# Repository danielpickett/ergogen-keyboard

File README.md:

# Pickett46 wireless split keyboard

A 46-key MX hot-swap keyboard with one nice!nano v2 per half and ZMK firmware.
The original Ergogen switch centers, rotations and 1.5u thumb positions are
preserved. Left and right have separate, fully routed two-layer PCBs.

## Fabrication files

- [Left JLCPCB ZIP](fabrication/pickett46-left-jlcpcb.zip)
- [Right JLCPCB ZIP](fabrication/pickett46-right-jlcpcb.zip)
- [Ordering details](docs/FABRICATION.md)
- [BOM](docs/BOM.csv) and [assembly instructions](docs/ASSEMBLY.md)
- [ZMK configuration, flashing and pin mapping](docs/FIRMWARE.md)

Both boards pass KiCad **9.0.2** DRC with **zero violations and zero unconnected
items**, with no DRC exclusions. The ZIPs also pass independent Gerber parsing,
layer/drill-count checks and source/hash checks. Both left/right firmware UF2s
were compiled successfully in Codex Cloud. These are digitally validated
fabrication outputs; a physical prototype has not been assembled or tested.

| Check | Left | Right |
|---|---:|---:|
| Keys / diodes | 23 / 23 | 23 / 23 |
| Copper layers | 2 | 2 |
| DRC violations | 0 | 0 |
| Unconnected items | 0 | 0 |
| Plated / non-plated drill hits | 59 / 119 | 59 / 119 |
| ZMK UF2 build | Pass | Pass |

## Editable sources and evidence

`hardware/left.kicad_pro` and `hardware/right.kicad_pro` open the production
boards in KiCad. All footprints are embedded in the PCB files; no external
footprint library is needed to edit or fabricate them. The adjacent `.kicad_dru`
files define manufacturing constraints and must stay beside the boards.

`config.yaml` is the active Ergogen layout. `footprints/` contains the custom
controller, reset and SOD-123 diode generators. `config-mine.yaml` is an unused
historical experiment. `config/` contains ZMK files; `firmware/` contains the
compiled images. `validation/` contains DRC, electrical/layout, mechanical,
Gerber and firmware evidence. `fabrication/manifest.json` records source and
ZIP SHA-256 hashes. `docs/previews/` shows actual exported copper and silk; the
bottom-layer images are shown through the board from the front, not mirrored
assembly views. `docs/plates/` contains the original-layout DXF switch cutouts.

## Reproduce or edit

Use Node.js with Ergogen 4.1.0, KiCad 9 CLI and KiCad's system Python `pcbnew` API.
All development and validation for this revision ran in Codex Cloud.

```sh
npm install
npm run build                 # unrouted scaffolds in output/pcbs
/usr/bin/python3 scripts/prepare_pcbs.py  # optional DSNs in output/kicad
bash scripts/validate.sh       # checks the committed routed hardware files
bash scripts/fabricate.sh      # validates, then exports both ZIPs
```

Ergogen generates placement and net assignments, **not finished copper**. The
committed `hardware/` boards additionally contain routing, antenna keepouts,
cleaned silkscreen and fabrication rules. The preparation script writes only
to `output/`, so it cannot silently replace the routed boards. After a layout
change, carry it into the production boards, reroute and rerun fabrication.
Specctra conversion rounds positions to 0.1 µm; the layout audit permits only
that rounding relative to the original layout saved from commit `7c6f7c1`.

For independent ZIP/mechanical checks, install
`scripts/requirements-validation.txt` in a Python virtual environment, then run:

```sh
python scripts/audit_exports.py
```

This parses the actual ZIPs and regenerates their SVG previews. KiCad's
Excellon output may produce a parser warning about G90 appearing after the
header; it is accepted and the drill coordinates and counts are checked.

Routing used Freerouting 2.1.0 plus final clearance-aware trace completion and
KiCad DRC cleanup. DRC clearance limits were not relaxed to make the boards pass.

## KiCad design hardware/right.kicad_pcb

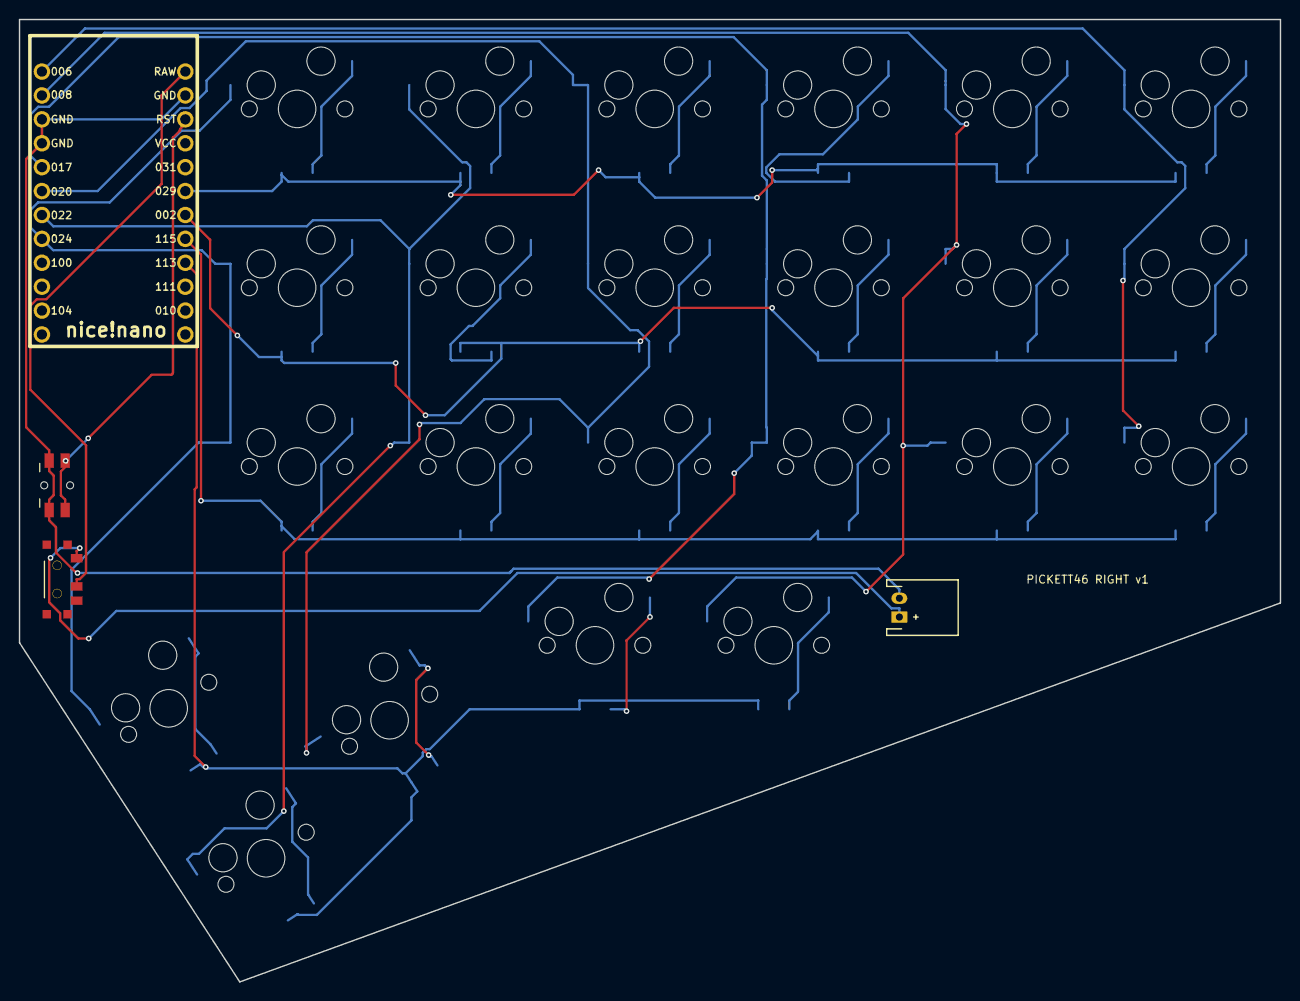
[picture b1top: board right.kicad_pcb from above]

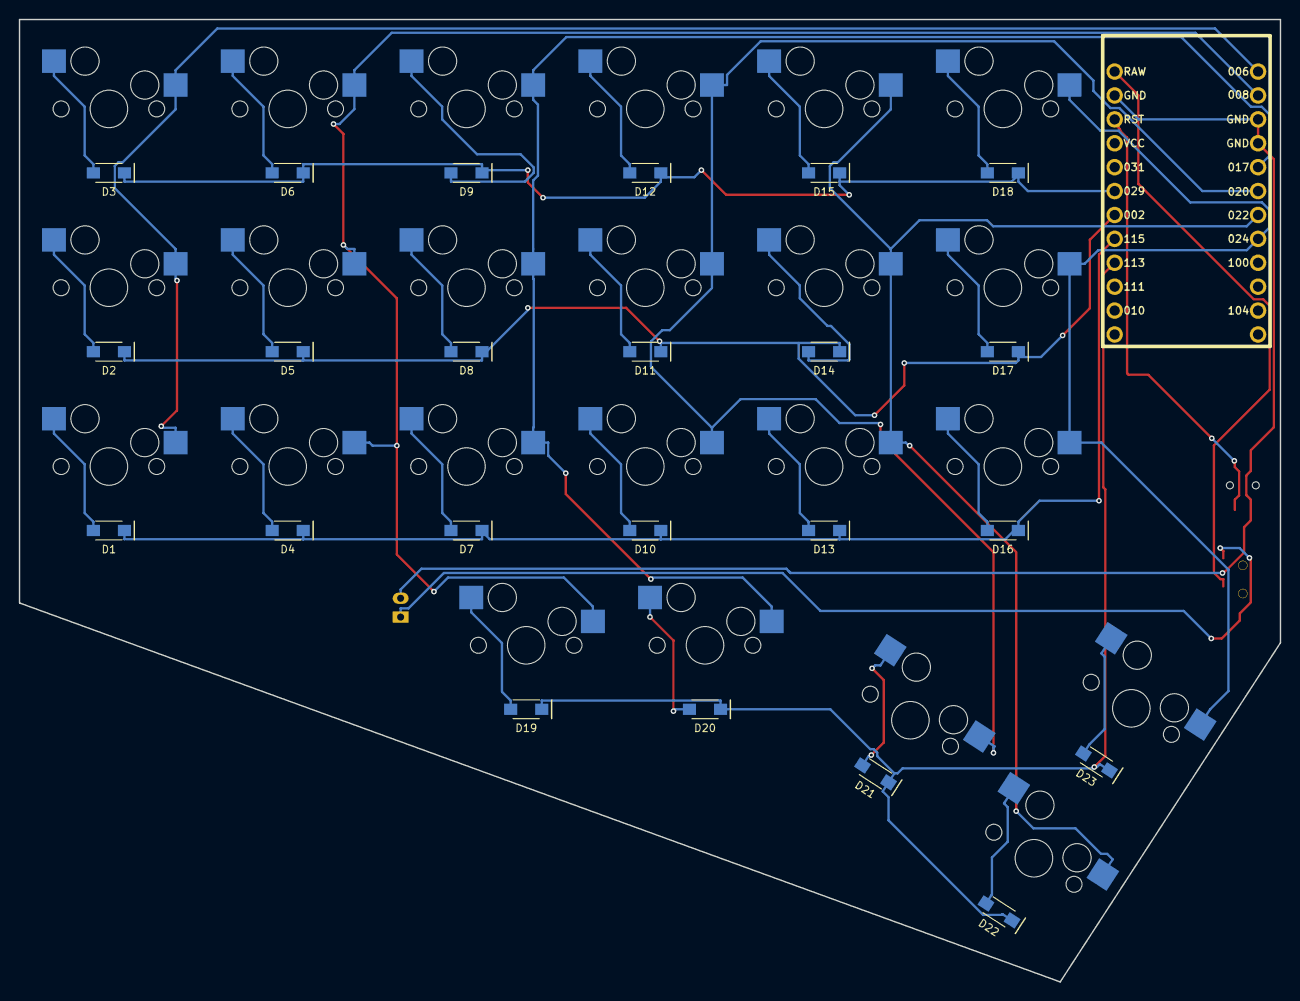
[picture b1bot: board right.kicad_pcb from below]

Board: 2 copper layers, 134.0 x 102.3 mm, 50 parts (23 on the bottom side), 37 nets.

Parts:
B1: Panasonic_EVQPUL_EVQPUC
D1, D2, D3, D4, D5, D6, D7, D8, D9, D10, D11, D12, D13, D14, D15, D16, D17, D18, D19, D20, D21, D22, D23: 1N4148W; D_SOD123
JST1: JST_PH_S2B-PH-K_02x2.00mm_Angled
MCU1: nice!nano v2, components up; nice_nano
S1, S2, S3, S4, S5, S6, S7, S8, S9, S10, S11, S12, S13, S14, S15, S16, S17, S18, S19, S20, S21, S22, S23: Kailh MX CPG151101S11; MX
T1: SPDT_C128955

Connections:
GND: B1.1, JST1.2, MCU1.3, MCU1.4, MCU1.23
P002: D2.1, D5.1, D8.1, D11.1, D14.1, D17.1, MCU1.18
P006: MCU1.1, S1.1, S2.1, S3.1
P008: MCU1.2, S4.1, S5.1, S6.1, S19.1
P017: MCU1.5, S7.1, S8.1, S9.1, S20.1
P020: MCU1.6, S10.1, S11.1, S12.1, S21.1
P022: MCU1.7, S13.1, S14.1, S15.1, S22.1
P024: MCU1.8, S16.1, S17.1, S18.1, S23.1
P029: D3.1, D6.1, D9.1, D12.1, D15.1, D18.1, MCU1.19
P113: D19.1, D20.1, D21.1, D22.1, D23.1, MCU1.16
P115: D1.1, D4.1, D7.1, D10.1, D13.1, D16.1, MCU1.17
RAW: MCU1.24, T1.2
RST: B1.2, MCU1.22
mirror_five_thumb: D23.2, S23.2
mirror_four_thumb: D22.2, S22.2
mirror_index_bottom: D13.2, S13.2
mirror_index_home: D14.2, S14.2
mirror_index_top: D15.2, S15.2
mirror_inner_bottom: D16.2, S16.2
mirror_inner_home: D17.2, S17.2
mirror_inner_top: D18.2, S18.2
mirror_middle_bottom: D10.2, S10.2
mirror_middle_home: D11.2, S11.2
mirror_middle_top: D12.2, S12.2
mirror_one_thumb: D19.2, S19.2
mirror_outer_bottom: D1.2, S1.2
mirror_outer_home: D2.2, S2.2
mirror_outer_top: D3.2, S3.2
mirror_pinky_bottom: D4.2, S4.2
mirror_pinky_home: D5.2, S5.2
mirror_pinky_top: D6.2, S6.2
mirror_ring_bottom: D7.2, S7.2
mirror_ring_home: D8.2, S8.2
mirror_ring_top: D9.2, S9.2
mirror_three_thumb: D21.2, S21.2
mirror_two_thumb: D20.2, S20.2
pos: JST1.1, T1.1

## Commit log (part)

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2024-09-28 initial config commit
2024-09-30 some updates
2024-09-30 merge
2024-10-30 starting from caldera and deleting stuff
2024-10-30 board outline not done, but was able to wire it up
2024-11-02 final nice_nano position; tighten up board outline
2024-11-02 remove reset switch
2024-11-02 tweak on/off switch and battery jack positions
2024-11-04 some tweaks
2024-11-04 git ignore tweak
2024-11-11 add right side PCB
